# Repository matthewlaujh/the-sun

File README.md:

# the sun — simulator

3D light simulator for a Ø1773 mm LED sun: 2,417 SK6812 RGBW pixels on 25 PCBs, inside the BIG LIGHT 9.1 assembly
(40×80 aluminium ring, wall mount, stand, 3 mm opal diffuser and an 8 mm cast-acrylic dome with a sanded outer face).

**Open `index.html`** — or the hosted copy on GitHub Pages once enabled. Everything is in the one file (Three.js is loaded from jsdelivr).

## What it does
- Renders every pixel at its KiCad position and lights it from the exact bytes that would go on the wire
  (pattern → master → cap 0.90 → gamma 2.2 → 8-bit RGBW), so what you see is what the PixLite E4-S receives.
- Physical diffuser model: cos⁴ screen law on the opal (≈56 mm equivalent height, ~50 % transmission) and on the
  dome (clear cast PMMA, 91 % LT @ 3 mm, outer face sanded), so blur grows from ~72 mm at the rim to ~280 mm at the centre.
- 52 patterns: *Rim ↔ dome* and *Dome studies* written for those optics, a few show patterns, and the four first-light tests.
- Output tab: power per PSU zone, frame stats, hover any LED for index / run / universe / channel / bytes.
- Live tab: point it at the ESP32-GATEWAY's WebSocket (raw 2417×4 frame or DDP packets) and it mirrors the real sun.
- Build tab: toggle assembly layers, exposure, room light; **Explode** slider pulls the layers apart.

## Control chain
Animation host (Olimex ESP32-GATEWAY, standalone AP + web server) → Ethernet → PixLite E4-S Mk3 in EXPANDED mode
→ 8 data runs → 25 boards. DDP on UDP :4048, byte offset = 4·i. `firmware/sun_map.h` carries the same map for C++.

## Layout
- `index.html` — the simulator (self-contained, 4.4 MB)
- `sun-map.json`, `sun-map.csv` — the authoritative pixel map
- `firmware/sun_map.h` — pixel map as C arrays (int16 mm×10) with universe/channel/zone helpers
- `source/` — `template.html` (the page before data is inlined), `sun_data.js` + `sun_model.js` (generated),
  `build_data.py` (map → data + header), `tess.py` / `export_model.py` (STEP → mesh pack), `assemble.py` (builds index.html)

## Rules baked in
Global brightness cap 0.90 · gamma 2.2 at output only · W channel for whites · hang rotation is view-only, pixels are never remapped.

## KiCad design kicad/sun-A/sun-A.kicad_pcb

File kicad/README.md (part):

# the sun — KiCad projects (draft 3)

Generated 2026-09-03 from the 2026-08-17 Studio DXF pack (sun-layout-dxf v2, on-line mounting).
Format: KiCad 8 s-expressions — KiCad 9 opens these and migrates them on save.

## Layout
- `sun-lib/` — shared symbols (`sun.kicad_sym`) + footprints (`sun.pretty/`)
- `sun-A/` — disc, 173 LEDs (172 + centre pixel), Ø448 mm
- `sun-B/` — wedge, 109 LEDs, r226→674, ×12
- `sun-C/` — wedge, 78 LEDs, r676→854, ×12
- per project: `.kicad_pro`, `.kicad_sch`, `.kicad_pcb`, `bom.csv`, `cpl.csv` (JLC format)

## Conventions (match Sun PCB Studio notes)
- Board coordinates: KiCad (x, y) = Studio/DXF (x, −y). No mirror: KiCad front = LED side = DXF view.
- **LED orientation is uniform-radial (draft 3.10)**: every LED's top edge (DIN/VDD side)
  faces AWAY from the sun centre, so the GND pad corner sits bottom-right radially on
  every LED, and every cap sits in the identical spot beside its LED's 5V pin
  (LED-local (−2.45, +4.40), long axis radial). Deviation from the Studio chain-rule pack.
- Data chain: LED pad2 DIN (+x local), pad4 DOUT (−x local); serpentine per Studio ROUTING layer.
- Nets: +5V (F.Cu pour), GND (B.Cu pour), D0 (J_IN→LED1), D1..D(n−1) chain, Dn (LEDn→J_OUT).
- WAGO 2601-3104 poles: **[5V | GND | GND | DATA]**, pads (1,2)(3,4)(5,6)(7,8); lever faces disc centre; **mounted on the BACK side** (same side as the standoffs, opposite the LEDs). Pole order runs mirrored vs a front mount — silk labels on the back read correctly from the wiring side.
- **WAGOs relocated clear of the mounting-plate strips** (30 mm skeleton members on the seam lines), deviation from the Studio pack:
  - **A**: the pair sits exactly diametrically opposite on the E–W line — J_IN at 0 deg (east), J_OUT at 180 deg (west), both at r = 192 mm, clear of the hub-spoke plates.
  - **B/C**: connectors are **docked parallel to their radial (wedge-cut) edge** — pole row along the edge direction, lever facing inboard. Pin-row centres 21.5 mm from the edge; courtyards ≥16 mm clear of the edge vs ~14 mm plate coverage.
- MH standoff footprints are true back-side footprints (placement side = Bottom).
- Standoffs: NPTH Ø4.22 + Ø6.2 pad on B.Cu (bottom reflow), net GND.
- A's DIN feed + C's DOUT return run on B.Cu through the GND pour (via at the LED end).

## Draft 3.15 changes (A connector centring + uniform standoff radius)
- **A's WAGO pair recentred**: pin centre moved from r195 to r199.06 so the
  connector BODY (which extends 10.4mm toward the lever/centre but only 2.3mm
  outward) sits exactly centred between rings 180 and 210; the pin centre was
  already the tangential midpoint of the two nearest LEDs. Still exactly
  opposite on the E-W axis. (Also fixed a sign bug in the placement search
  that tested the courtyard mirrored to the wrong side of the pins.)
- **A's six outer standoffs normalised to a common r=215** (slid inward along
  their radial skeleton members, angles unchanged): the Studio pack had five
  at ~218.5 with the copper moat ON the board edge and one at 215. Now every
  hole has the same ~5.9mm pad-to-edge and 3.5mm moat-to-edge margin.
  WARNING: the matching frame holes move 3.5mm inward on five spokes - update
  the skeleton drawing.

- **No trace under any LED or cap body — either layer** (3.16): LED/cap
  courtyards now keep out foreign traces on the BACK copper too, so the long
  back-layer runs (feeds/returns) weave between footprints instead of passing
  under them. Verified: zero back-copper crossings of any LED/cap body.
- **Pad exits run straight before turning** (3.16): exit stubs lengthened to
  2.5mm from pad centre (~1.75mm beyond the pad edge) and protected from the
  corner-smoothing pass; wrap/jog hooks land with a 1.5mm straight run into
  the DIN pad. Applies across all designs.
- **Fallback links smoothed into curves**: row-to-row jumps and dogleg hops
  (the paths the generic router produces near connectors and standoffs) now go
  through a clearance-validated corner-rounding pass, so they flow like the
  patterned links instead of showing chamfered elbows.

## Draft 3.14 changes (silk-free LED face)
- **All front silkscreen removed** except one mark per LED: the standard
  pin-1/GND TRIANGLE (0.7 mm, filled) tucked UNDER the package body with its
  tip pointing at pad 1 — visible on the bare board for orientation checks,
  completely hidden once the LED is soldered.
- Cap outlines, MH rings, and the front board title are gone; the JLC
  order-number placeholder ("JLCJLCJLCJLC") moved to the BACK silk so JLC's
  print can't land on the front. Board id stays on the back. WAGO pole labels
  (5V/G/G/D), lever mark and pin-1 dot stay on the back silk for hand-wiring.

## Draft 3.13 changes (A chain matches design pack 3)
- Board A's data chain re-ordered to match **sunleddesignpack 3**: the centre LED
  is now the FIRST pixel (universe 1, channel 1) and the serpentine runs in the
  pack-3 (mirrored) direction. LED refs 1..173 = pack3's LED1..173 exactly, so
  the pack's dmx-patch.csv / led-map.csv apply with no hand edits.
  Feed: J_IN -> centre on the back layer; return: LED173 (ring 210) -> J_OUT.
- Only output 1's boards shift in the pack's patch; outputs 2-4 are untouched.
- Mounting stays the BZXC / Ø4.22 layout (user choice; the pack's SMTSO scheme
  was NOT adopted) — centre standoff remains deleted (the centre LED sits there).

## Draft 3.12 changes (isolated mounting holes + A centre pixel)
- **Every mounting hole is now electrically ISOLATED**: the standoff's B.Cu solder
  pad has no net, and a copper-free moat (Ø11 mm keep-out ring, both layers) keeps
  the pours away — a screw scratching through the mask can't short 5V/GND.
  Traces additionally keep ≥3.0 mm from every hole edge (verified ≥2.8).
  Schematic MH pins carry no-connect markers. Standoffs float (not grounded).
- **Board A: centre mounting hole removed, LED173 added at the exact centre** as
  the LAST pixel of the chain (user choice: existing pixel addresses unchanged;
  the new pixel simply appends as A's pixel #173, channels 689-692 in A's map).
  LED172→LED173 runs as a 2-via back-side radial drop; the return LED173→J_OUT
  is a straight back-side shot due west. A now has 173 LEDs, 173 caps, 6 standoffs.

## Draft 3.11 changes (clearances + standoff keep-away)
- **Routing clearances raised** (user: safety margin): trace-to-copper routing target
  0.45 mm (DRC net class stays 0.35 — everything routes with ≥0.1 mm DRC margin),
  courtyard keep-out margin 0.5 mm, and **standoff holes keep all copper ≥2.4 mm
  from the hole edge** (verified ≥2.2 mm; JLC minimum is 0.3).
- No trace passes near a mounting hole any more: a wrap whose band would come
  near a standoff flips to the inward lane, and where the in/out alternation
  can't absorb that, the link takes a short, deterministic **2-via back-side
  jog** instead (A: 3 jogs, B: 1 jog at the row-98→99 jump, C: none).
- Ground stitching: not added — the B.Cu GND plane is the only ground plane
  (F.Cu carries the 5V pour), and the TWO GND vias at every LED (~350/220/160
  per board) already tie front copper to it at ~30 mm pitch everywhere.

## Draft 3.10 changes (uniform LED orientation)
- All LEDs re-oriented to the uniform-radial convention above (same footprint spots,
  the 90/180-degree branch of each rotation re-picked). CPL rotations updated.
- With uniform orientation, in the rings where the chain runs against the LED's
  DOUT→DIN direction the link cannot go straight. Those links use **front-side
  wraps, no vias**: alternating between an inward lane below the row (r_row − 3.75)
  and an outward band above the cap row (r_row + 6.6), as smooth polar arcs.
  Adjacent wraps alternate in/out so nothing crosses.
- The outward band **bulges smoothly around the NPTH standoffs** (4.15 mm keep-out
  envelope with a 2.5 mm ramp) where a mounting hole sits in its path.
- GND vias moved to uniform spots: LED GND via at LED-local (2.45, −2.55) tucked
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
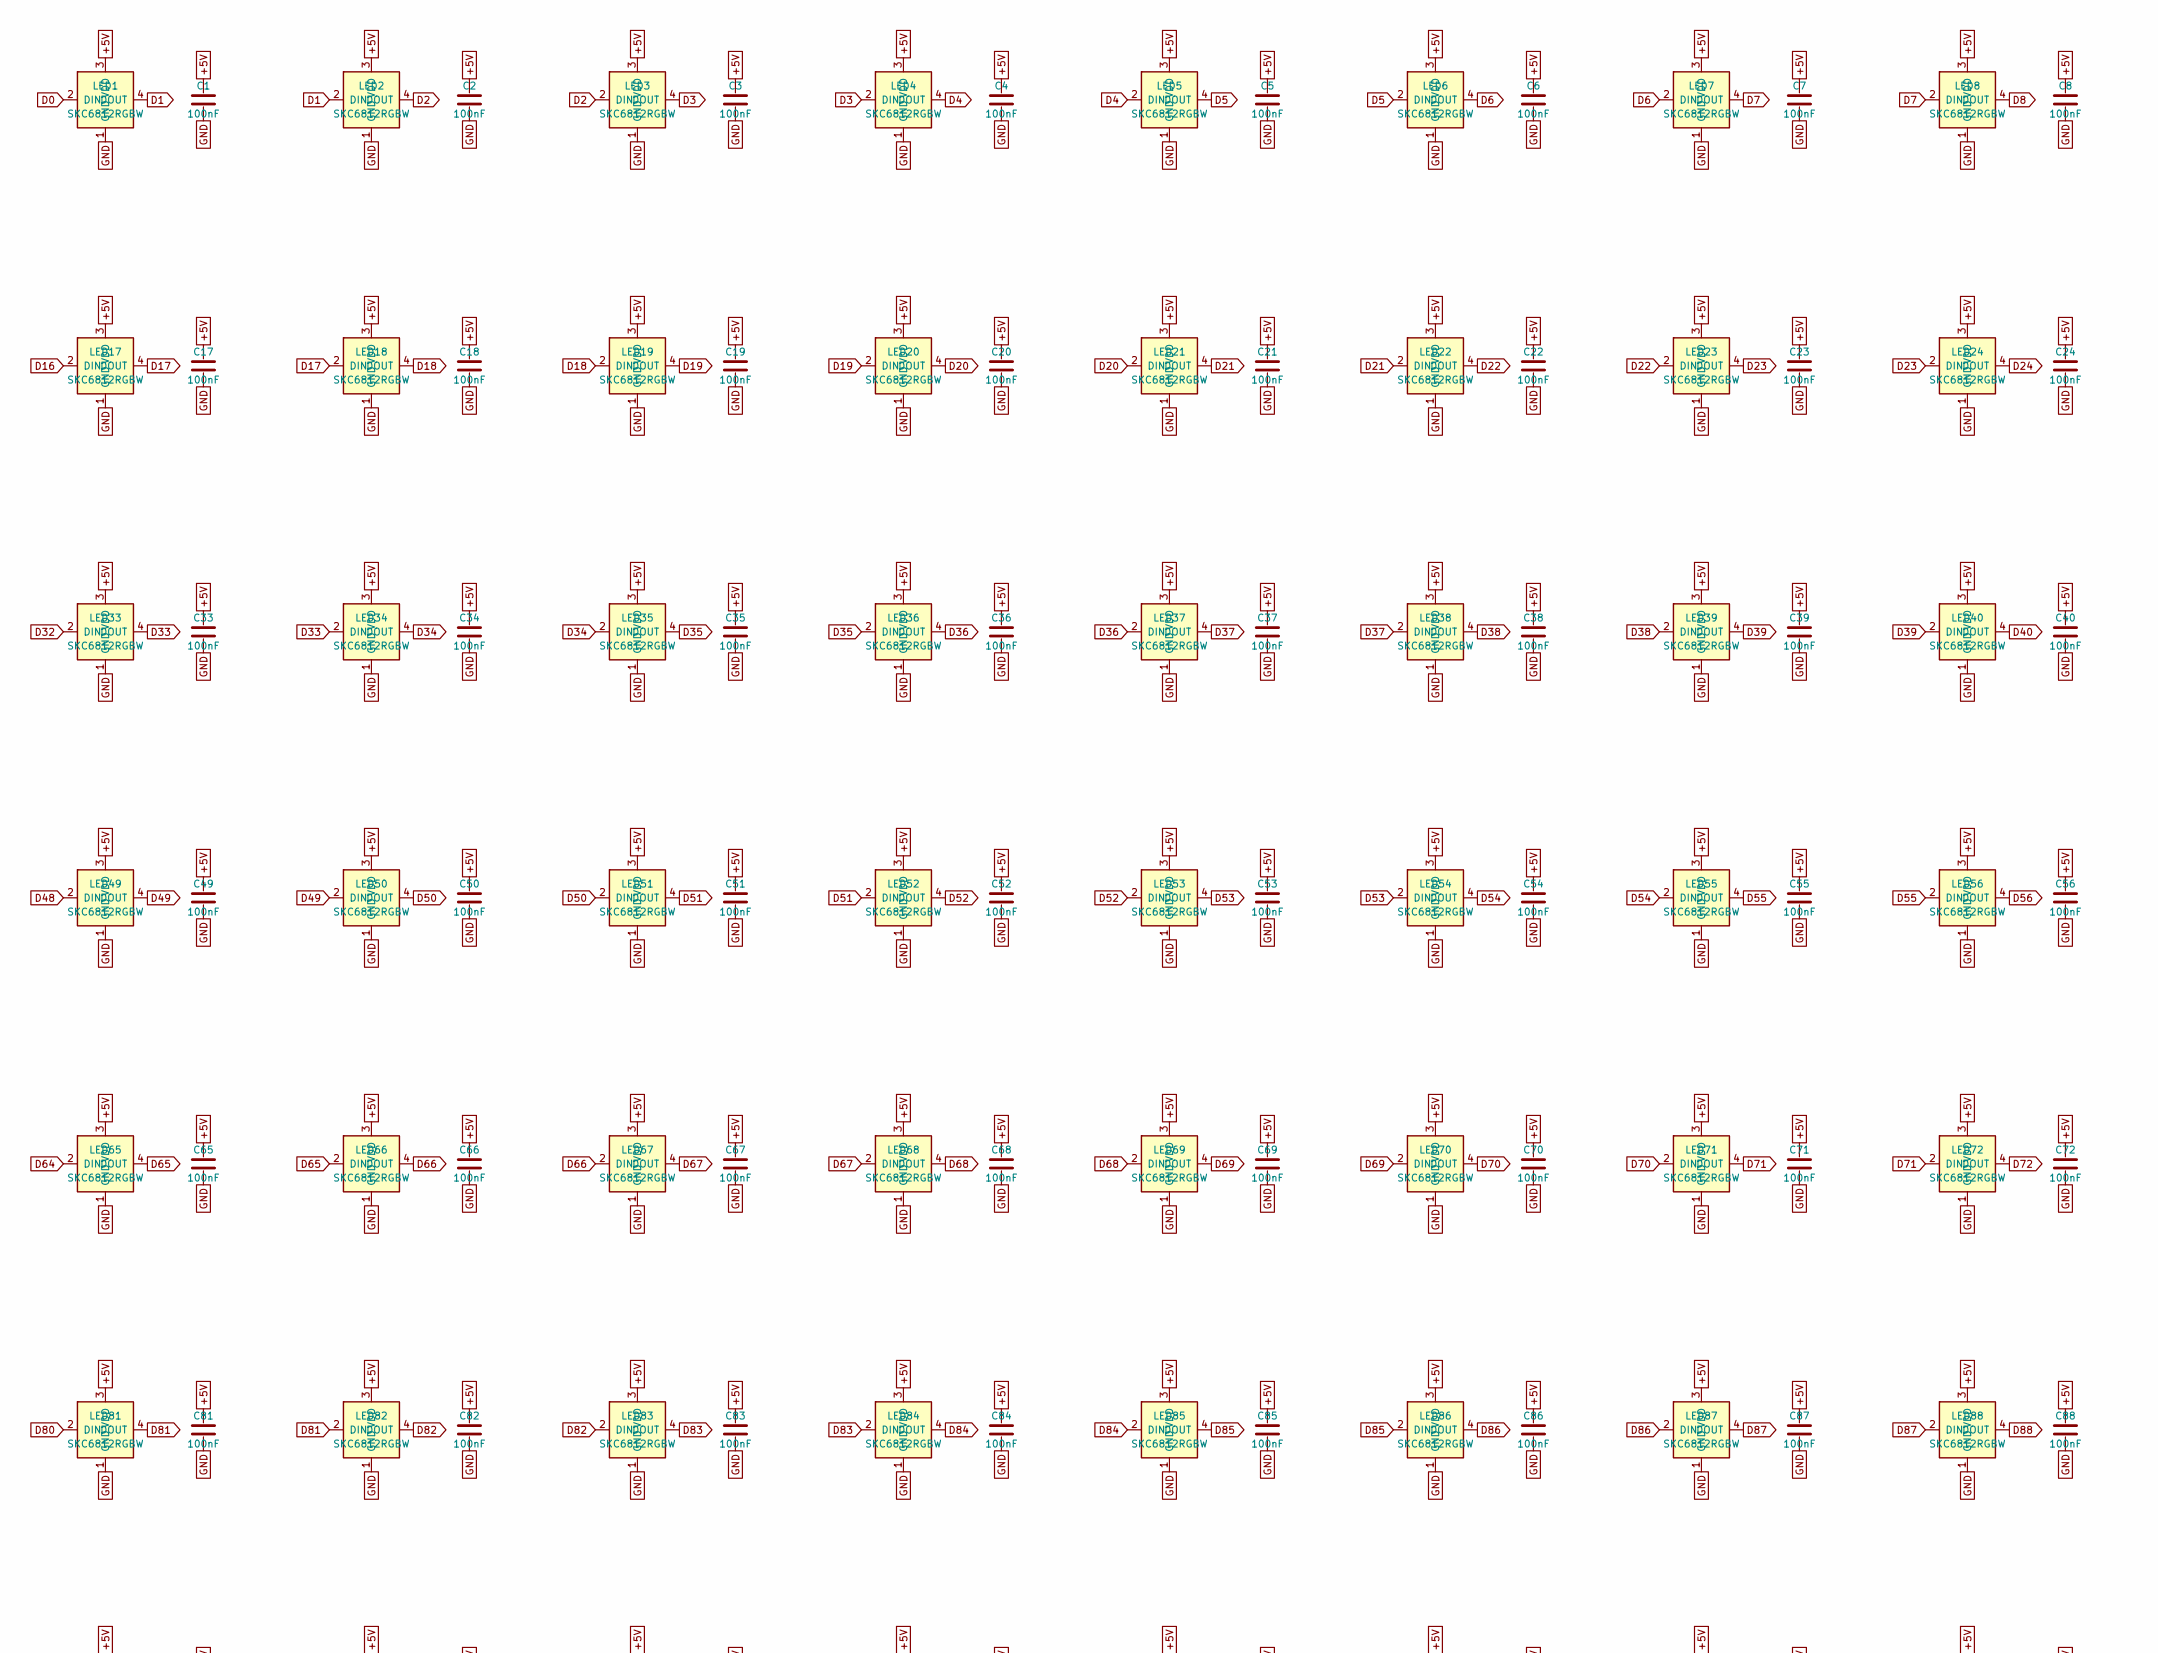
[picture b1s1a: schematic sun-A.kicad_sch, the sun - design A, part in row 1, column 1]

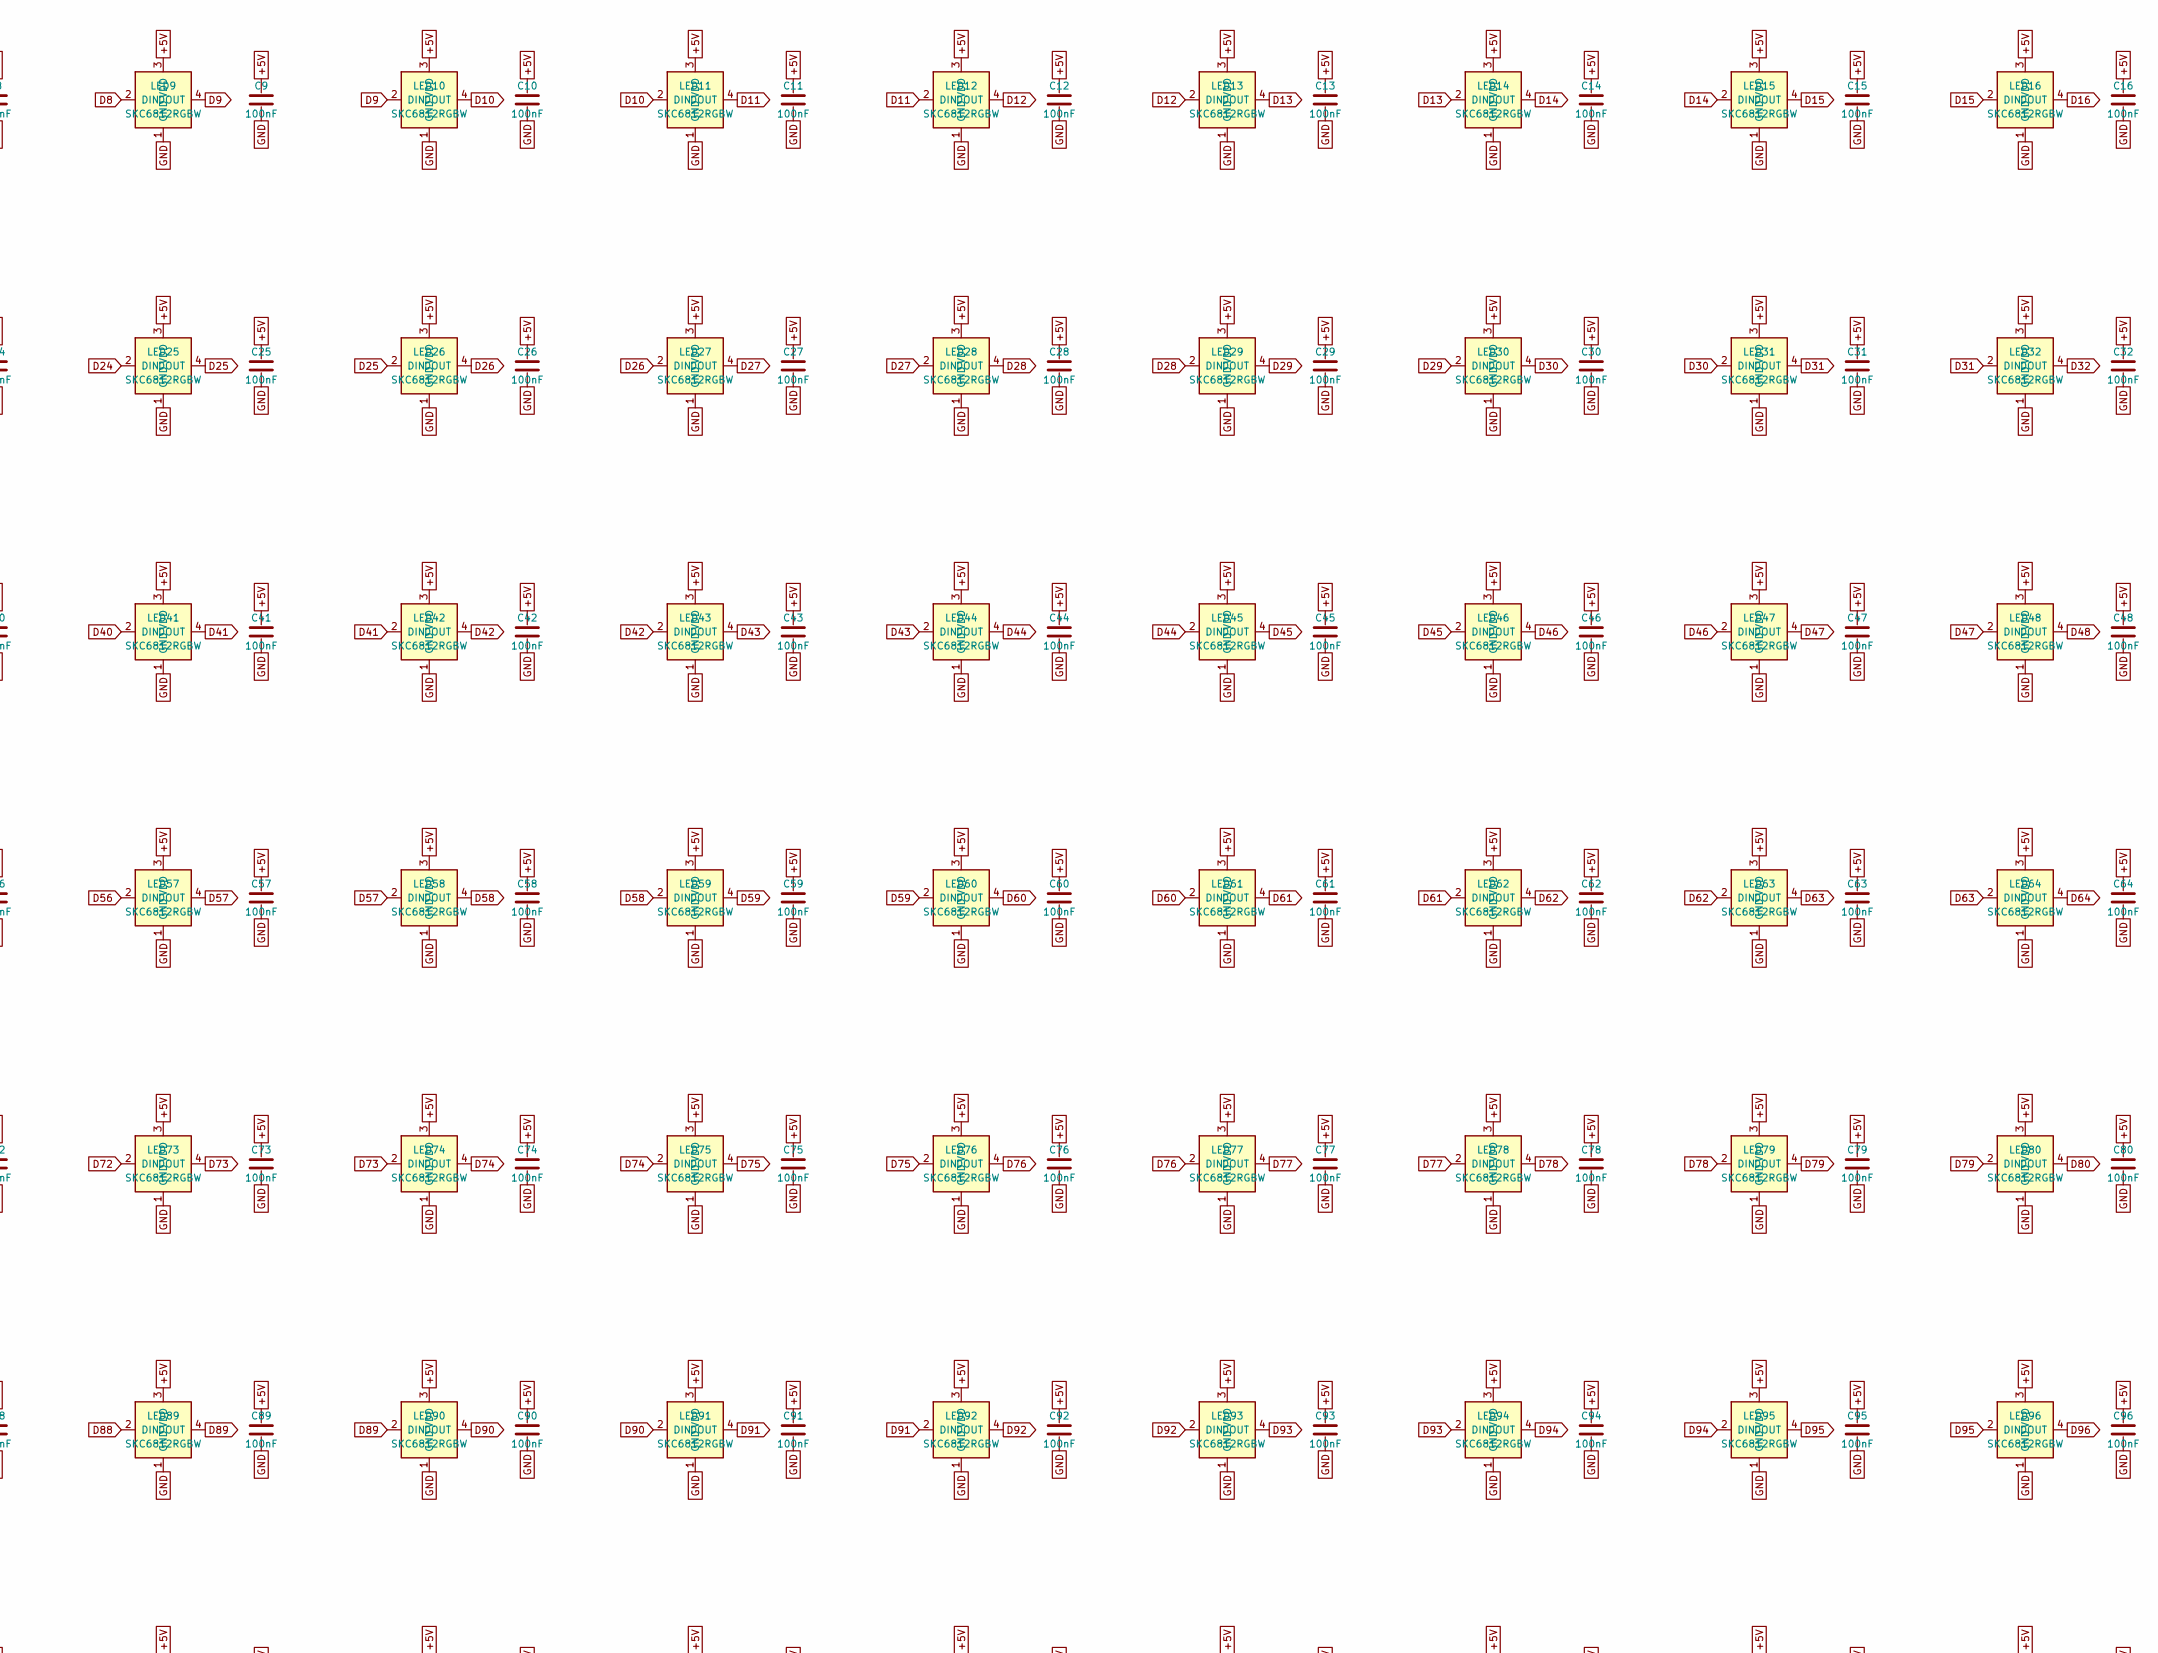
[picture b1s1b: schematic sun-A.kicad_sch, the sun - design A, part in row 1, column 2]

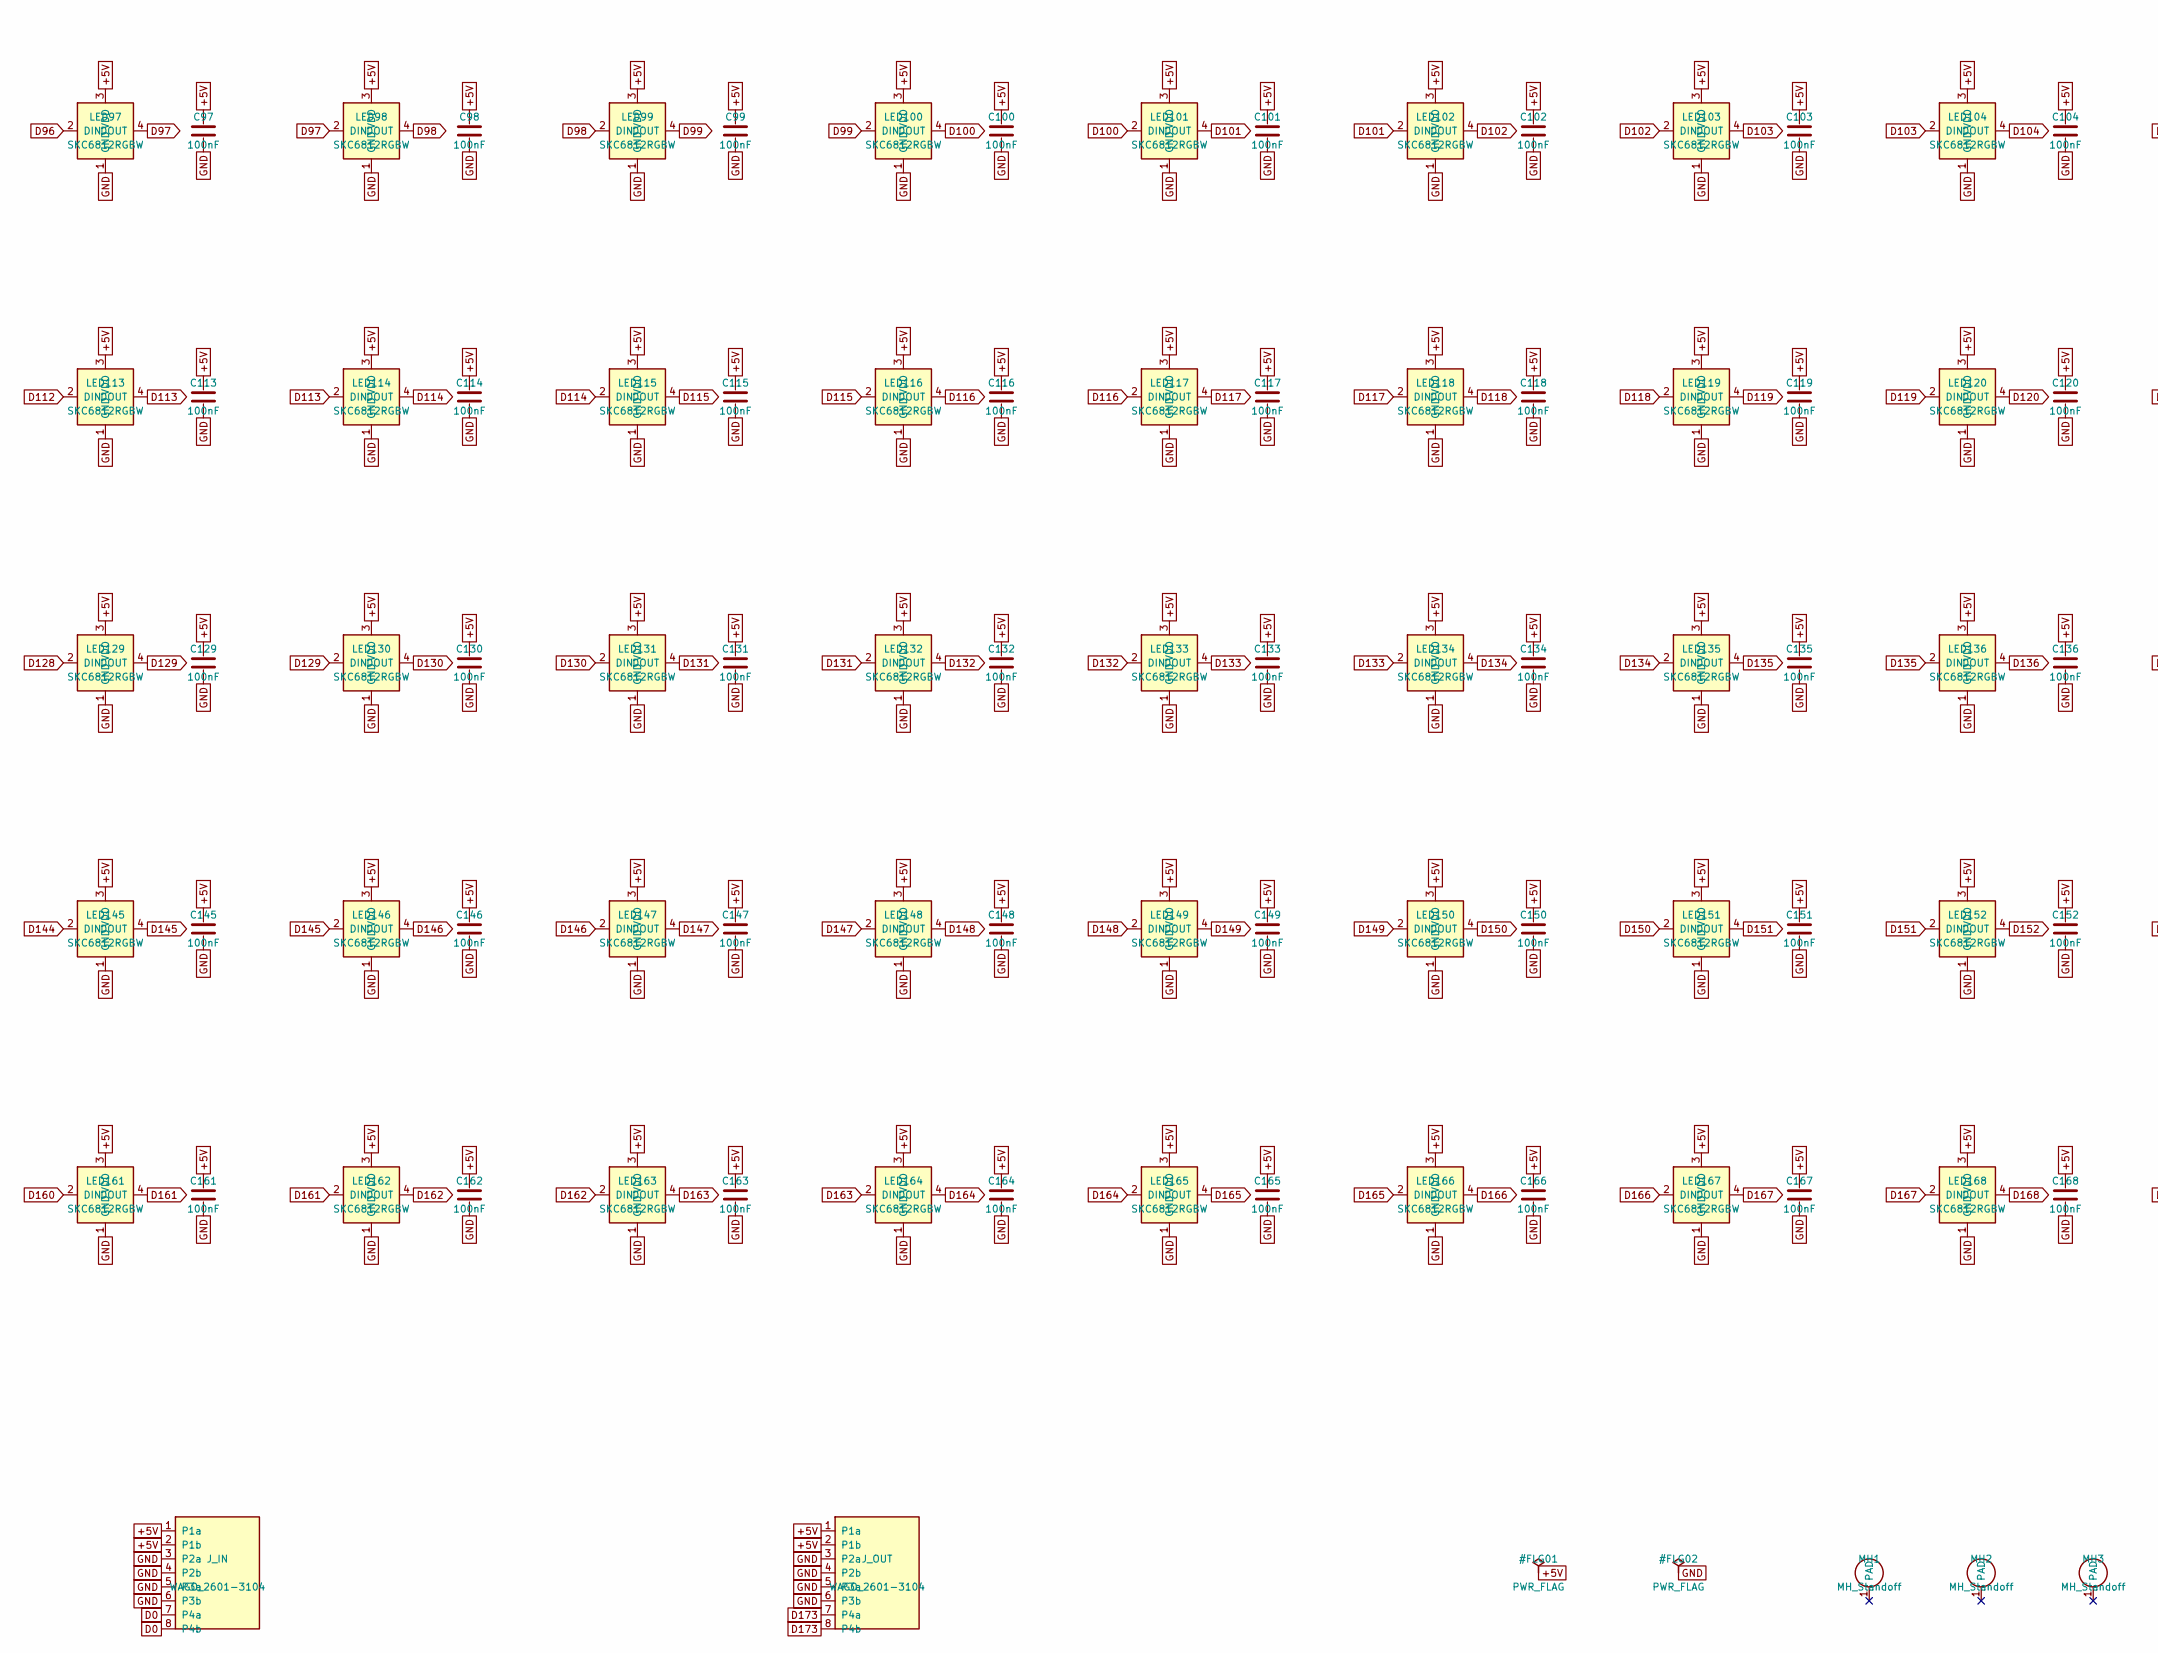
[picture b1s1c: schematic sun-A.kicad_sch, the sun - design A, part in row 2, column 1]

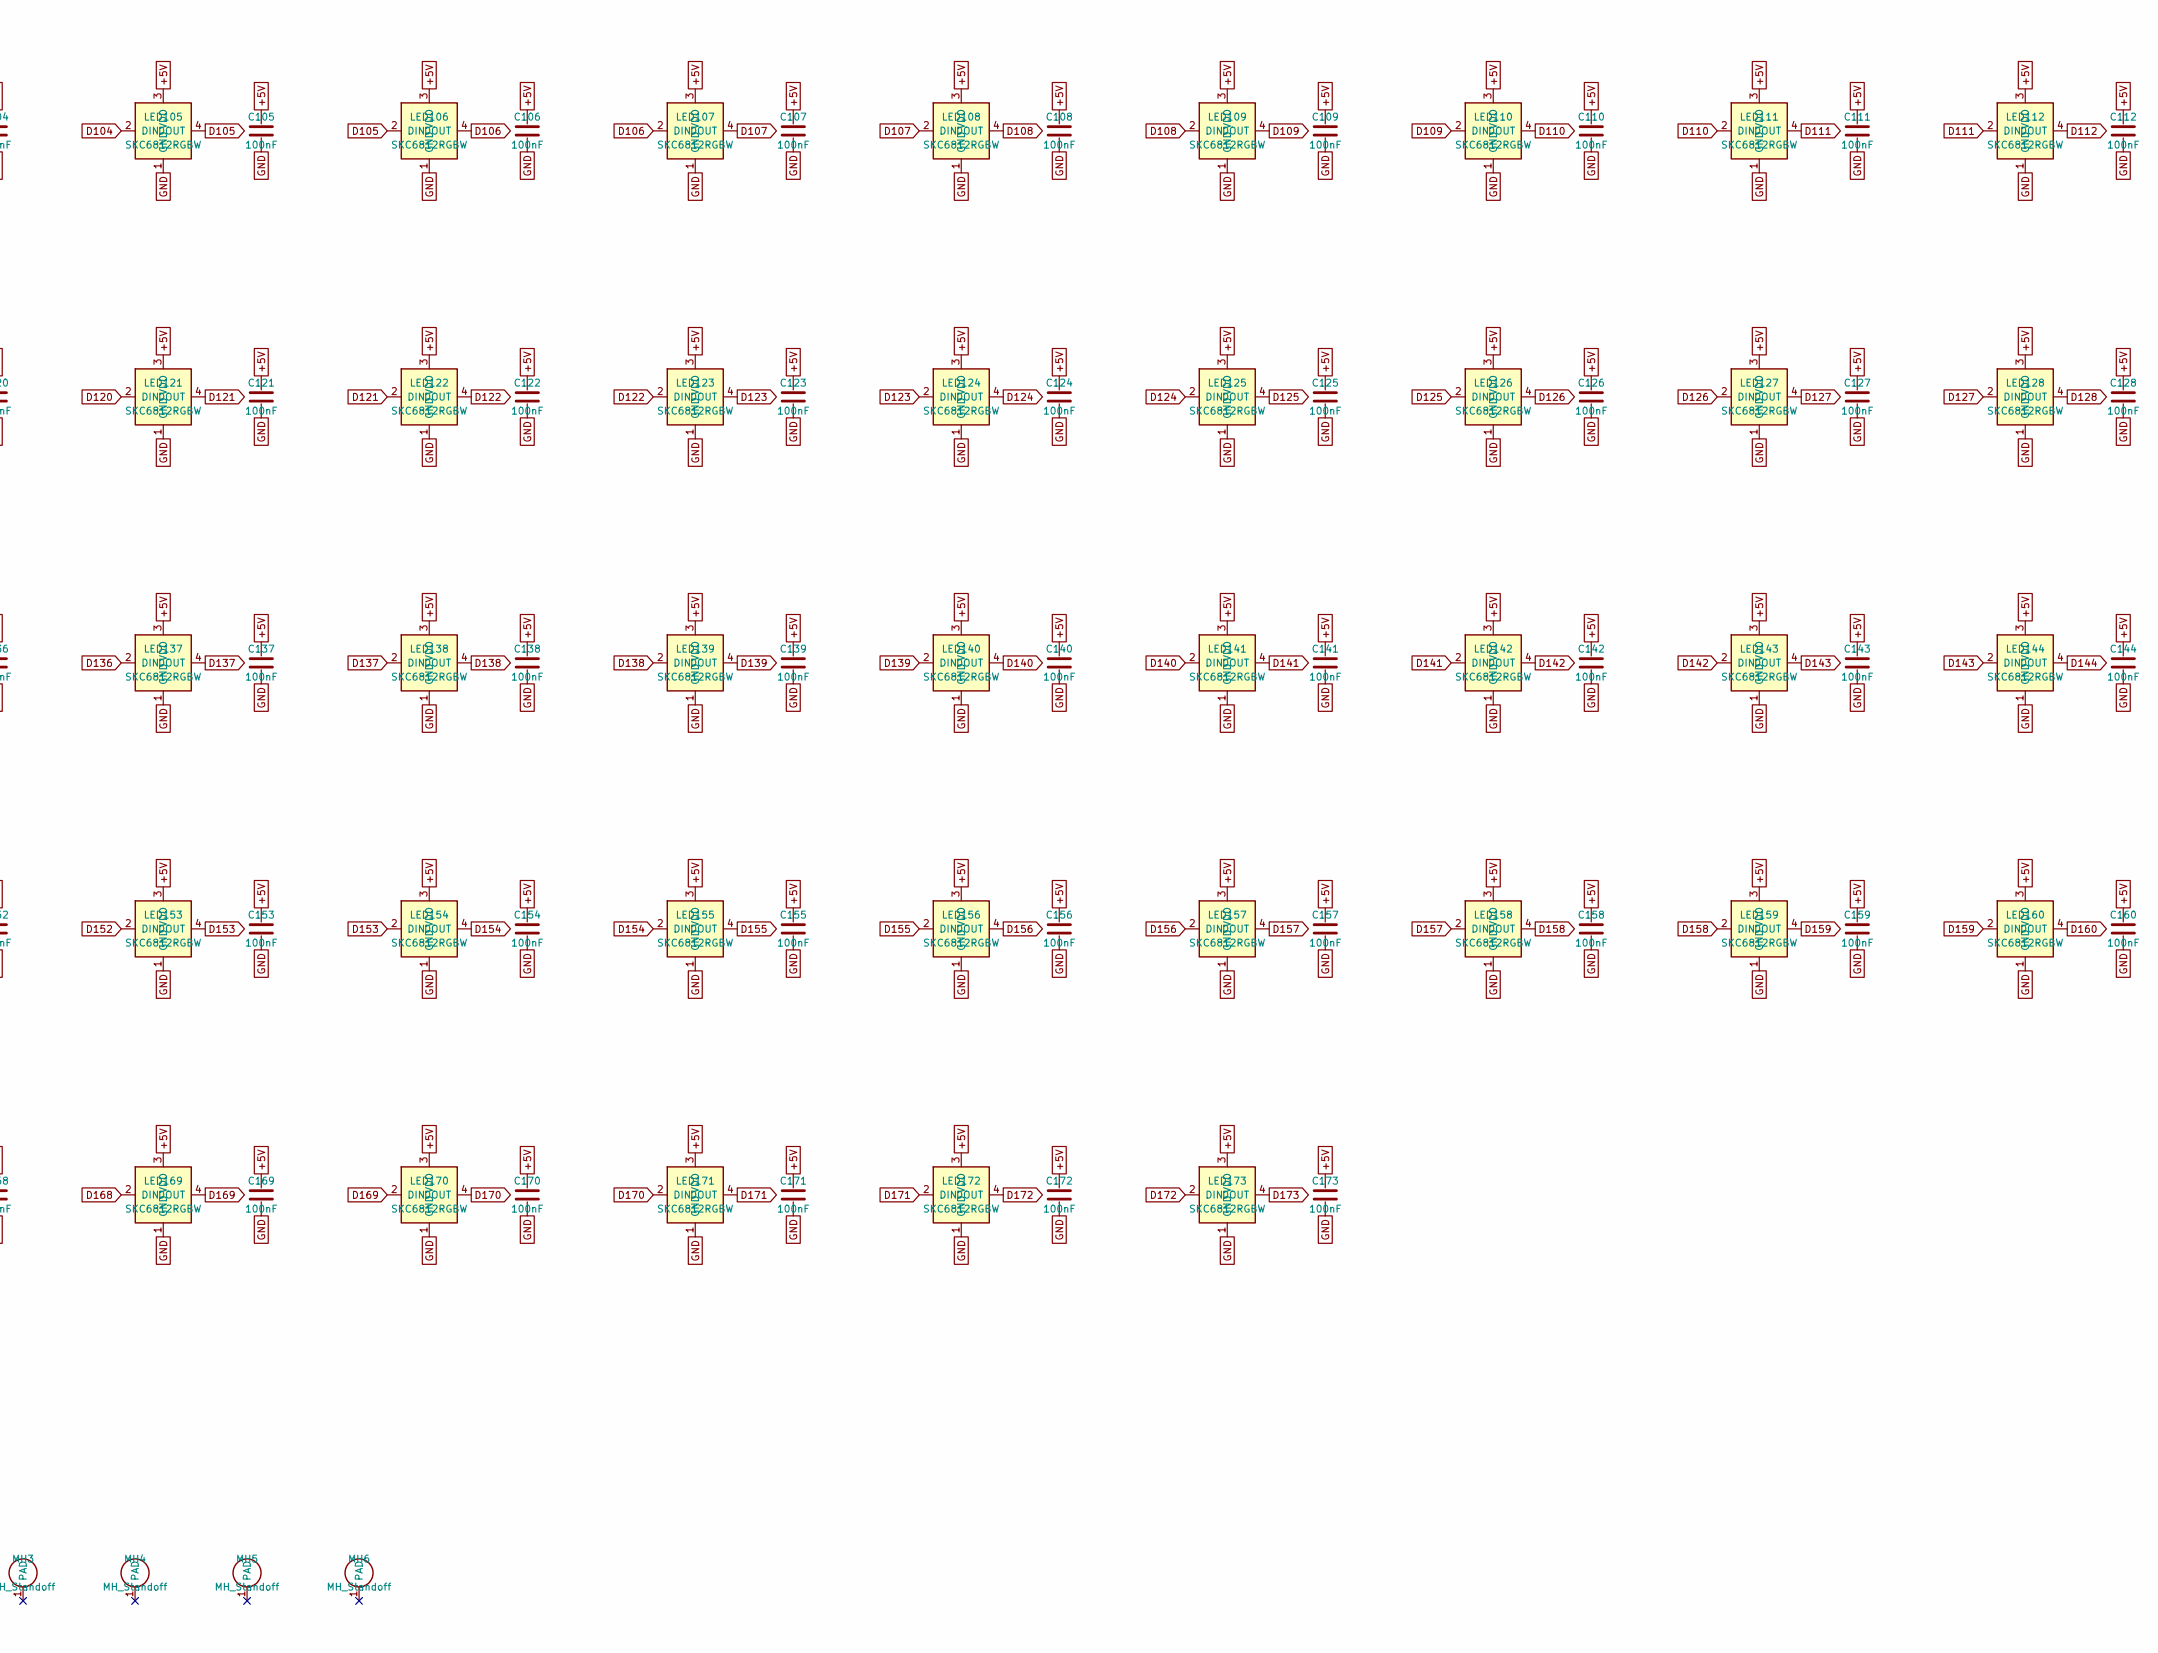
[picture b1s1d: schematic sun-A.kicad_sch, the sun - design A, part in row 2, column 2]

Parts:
C1, C2, C3, C4, C5, C6, C7, C8, C9, C10, C11, C12, C13, C14, C15, C16, C17, C18, C19, C20, C21, C22, C23, C24, C25, C26, C27, C28, C29, C30, C31, C32, C33, C34, C35, C36, C37, C38, C39, C40, C41, C42, C43, C44, C45, C46, C47, C48, C49, C50, C51, C52, C53, C54, C55, C56, C57, C58, C59, C60, C61, C62, C63, C64, C65, C66, C67, C68, C69, C70, C71, C72, C73, C74, C75, C76, C77, C78, C79, C80, C81, C82, C83, C84, C85, C86, C87, C88, C89, C90, C91, C92, C93, C94, C95, C96, C97, C98, C99, C100, C101, C102, C103, C104, C105, C106, C107, C108, C109, C110, C111, C112, C113, C114, C115, C116, C117, C118, C119, C120, C121, C122, C123, C124, C125, C126, C127, C128, C129, C130, C131, C132, C133, C134, C135, C136, C137, C138, C139, C140, C141, C142, C143, C144, C145, C146, C147, C148, C149, C150, C151, C152, C153, C154, C155, C156, C157, C158, C159, C160, C161, C162, C163, C164, C165, C166, C167, C168, C169, C170, C171, C172, C173: 100nF; C_0603_1608Metric; LCSC C1591
J_IN: WAGO_2601-3104; WAGO_2601-3104_THT
J_OUT: WAGO_2601-3104; WAGO_2601-3104_THT
LED1, LED2, LED3, LED4, LED5, LED6, LED7, LED8, LED9, LED10, LED11, LED12, LED13, LED14, LED15, LED16, LED17, LED18, LED19, LED20, LED21, LED22, LED23, LED24, LED25, LED26, LED27, LED28, LED29, LED30, LED31, LED32, LED33, LED34, LED35, LED36, LED37, LED38, LED39, LED40, LED41, LED42, LED43, LED44, LED45, LED46, LED47, LED48, LED49, LED50, LED51, LED52, LED53, LED54, LED55, LED56, LED57, LED58, LED59, LED60, LED61, LED62, LED63, LED64, LED65, LED66, LED67, LED68, LED69, LED70, LED71, LED72, LED73, LED74, LED75, LED76, LED77, LED78, LED79, LED80, LED81, LED82, LED83, LED84, LED85, LED86, LED87, LED88, LED89, LED90, LED91, LED92, LED93, LED94, LED95, LED96, LED97, LED98, LED99, LED100, LED101, LED102, LED103, LED104, LED105, LED106, LED107, LED108, LED109, LED110, LED111, LED112, LED113, LED114, LED115, LED116, LED117, LED118, LED119, LED120, LED121, LED122, LED123, LED124, LED125, LED126, LED127, LED128, LED129, LED130, LED131, LED132, LED133, LED134, LED135, LED136, LED137, LED138, LED139, LED140, LED141, LED142, LED143, LED144, LED145, LED146, LED147, LED148, LED149, LED150, LED151, LED152, LED153, LED154, LED155, LED156, LED157, LED158, LED159, LED160, LED161, LED162, LED163, LED164, LED165, LED166, LED167, LED168, LED169, LED170, LED171, LED172, LED173: SKC6812RGBW; LED_SKC6812RGBW_5050; LCSC C5348912
MH1, MH2, MH3, MH4, MH5, MH6: MH_Standoff; MH_M3_SMT_Standoff_BZXC; LCSC C20617225 (3mm; 30mm variant TBC)

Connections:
+5V: C1.1, C2.1, C3.1, C4.1, C5.1, C6.1, C7.1, C8.1, C9.1, C10.1, C11.1, C12.1, C13.1, C14.1, C15.1, C16.1, C17.1, C18.1, C19.1, C20.1, C21.1, C22.1, C23.1, C24.1, C25.1, C26.1, C27.1, C28.1, C29.1, C30.1, C31.1, C32.1, C33.1, C34.1, C35.1, C36.1, C37.1, C38.1, C39.1, C40.1, C41.1, C42.1, C43.1, C44.1, C45.1, C46.1, C47.1, C48.1, C49.1, C50.1, C51.1, C52.1, C53.1, C54.1, C55.1, C56.1, C57.1, C58.1, C59.1, C60.1, C61.1, C62.1, C63.1, C64.1, C65.1, C66.1, C67.1, C68.1, C69.1, C70.1, C71.1, C72.1, C73.1, C74.1, C75.1, C76.1, C77.1, C78.1, C79.1, C80.1, C81.1, C82.1, C83.1, C84.1, C85.1, C86.1, C87.1, C88.1, C89.1, C90.1, C91.1, C92.1, C93.1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
D0: J_IN.7 (P4a), J_IN.8 (P4b), LED1.2 (DIN)
D1: LED1.4 (DOUT), LED2.2 (DIN)
D2: LED2.4 (DOUT), LED3.2 (DIN)
D3: LED3.4 (DOUT), LED4.2 (DIN)
D4: LED4.4 (DOUT), LED5.2 (DIN)
D5: LED5.4 (DOUT), LED6.2 (DIN)
D6: LED6.4 (DOUT), LED7.2 (DIN)
D7: LED7.4 (DOUT), LED8.2 (DIN)
D8: LED8.4 (DOUT), LED9.2 (DIN)
D9: LED9.4 (DOUT), LED10.2 (DIN)
D10: LED10.4 (DOUT), LED11.2 (DIN)
D11: LED11.4 (DOUT), LED12.2 (DIN)
D12: LED12.4 (DOUT), LED13.2 (DIN)
D13: LED13.4 (DOUT), LED14.2 (DIN)
D14: LED14.4 (DOUT), LED15.2 (DIN)
D15: LED15.4 (DOUT), LED16.2 (DIN)
D16: LED16.4 (DOUT), LED17.2 (DIN)
D17: LED17.4 (DOUT), LED18.2 (DIN)
D18: LED18.4 (DOUT), LED19.2 (DIN)
D19: LED19.4 (DOUT), LED20.2 (DIN)
D20: LED20.4 (DOUT), LED21.2 (DIN)
D21: LED21.4 (DOUT), LED22.2 (DIN)
D22: LED22.4 (DOUT), LED23.2 (DIN)
D23: LED23.4 (DOUT), LED24.2 (DIN)
D24: LED24.4 (DOUT), LED25.2 (DIN)
D25: LED25.4 (DOUT), LED26.2 (DIN)
D26: LED26.4 (DOUT), LED27.2 (DIN)
D27: LED27.4 (DOUT), LED28.2 (DIN)
D28: LED28.4 (DOUT), LED29.2 (DIN)
D29: LED29.4 (DOUT), LED30.2 (DIN)
D30: LED30.4 (DOUT), LED31.2 (DIN)
D31: LED31.4 (DOUT), LED32.2 (DIN)
D32: LED32.4 (DOUT), LED33.2 (DIN)
D33: LED33.4 (DOUT), LED34.2 (DIN)
D34: LED34.4 (DOUT), LED35.2 (DIN)
D35: LED35.4 (DOUT), LED36.2 (DIN)
D36: LED36.4 (DOUT), LED37.2 (DIN)
D37: LED37.4 (DOUT), LED38.2 (DIN)
D38: LED38.4 (DOUT), LED39.2 (DIN)
D39: LED39.4 (DOUT), LED40.2 (DIN)
D40: LED40.4 (DOUT), LED41.2 (DIN)
D41: LED41.4 (DOUT), LED42.2 (DIN)
D42: LED42.4 (DOUT), LED43.2 (DIN)
D43: LED43.4 (DOUT), LED44.2 (DIN)
D44: LED44.4 (DOUT), LED45.2 (DIN)
D45: LED45.4 (DOUT), LED46.2 (DIN)
D46: LED46.4 (DOUT), LED47.2 (DIN)
D47: LED47.4 (DOUT), LED48.2 (DIN)
D48: LED48.4 (DOUT), LED49.2 (DIN)
D49: LED49.4 (DOUT), LED50.2 (DIN)
D50: LED50.4 (DOUT), LED51.2 (DIN)
D51: LED51.4 (DOUT), LED52.2 (DIN)
D52: LED52.4 (DOUT), LED53.2 (DIN)
D53: LED53.4 (DOUT), LED54.2 (DIN)
D54: LED54.4 (DOUT), LED55.2 (DIN)
D55: LED55.4 (DOUT), LED56.2 (DIN)
D56: LED56.4 (DOUT), LED57.2 (DIN)
D57: LED57.4 (DOUT), LED58.2 (DIN)
D58: LED58.4 (DOUT), LED59.2 (DIN)
D59: LED59.4 (DOUT), LED60.2 (DIN)
D60: LED60.4 (DOUT), LED61.2 (DIN)
D61: LED61.4 (DOUT), LED62.2 (DIN)
D62: LED62.4 (DOUT), LED63.2 (DIN)
D63: LED63.4 (DOUT), LED64.2 (DIN)
D64: LED64.4 (DOUT), LED65.2 (DIN)
D65: LED65.4 (DOUT), LED66.2 (DIN)
D66: LED66.4 (DOUT), LED67.2 (DIN)
D67: LED67.4 (DOUT), LED68.2 (DIN)
D68: LED68.4 (DOUT), LED69.2 (DIN)
D69: LED69.4 (DOUT), LED70.2 (DIN)
D70: LED70.4 (DOUT), LED71.2 (DIN)
D71: LED71.4 (DOUT), LED72.2 (DIN)
D72: LED72.4 (DOUT), LED73.2 (DIN)
D73: LED73.4 (DOUT), LED74.2 (DIN)
D74: LED74.4 (DOUT), LED75.2 (DIN)
D75: LED75.4 (DOUT), LED76.2 (DIN)
D76: LED76.4 (DOUT), LED77.2 (DIN)
D77: LED77.4 (DOUT), LED78.2 (DIN)
D78: LED78.4 (DOUT), LED79.2 (DIN)
D79: LED79.4 (DOUT), LED80.2 (DIN)
D80: LED80.4 (DOUT), LED81.2 (DIN)
D81: LED81.4 (DOUT), LED82.2 (DIN)
D82: LED82.4 (DOUT), LED83.2 (DIN)
D83: LED83.4 (DOUT), LED84.2 (DIN)
D84: LED84.4 (DOUT), LED85.2 (DIN)
D85: LED85.4 (DOUT), LED86.2 (DIN)
D86: LED86.4 (DOUT), LED87.2 (DIN)
D87: LED87.4 (DOUT), LED88.2 (DIN)
D88: LED88.4 (DOUT), LED89.2 (DIN)
D89: LED89.4 (DOUT), LED90.2 (DIN)
D90: LED90.4 (DOUT), LED91.2 (DIN)
D91: LED91.4 (DOUT), LED92.2 (DIN)
D92: LED92.4 (DOUT), LED93.2 (DIN)
D93: LED93.4 (DOUT), LED94.2 (DIN)
D94: LED94.4 (DOUT), LED95.2 (DIN)
D95: LED95.4 (DOUT), LED96.2 (DIN)
D96: LED96.4 (DOUT), LED97.2 (DIN)
D97: LED97.4 (DOUT), LED98.2 (DIN)
D98: LED98.4 (DOUT), LED99.2 (DIN)
D99: LED99.4 (DOUT), LED100.2 (DIN)
D100: LED100.4 (DOUT), LED101.2 (DIN)
D101: LED101.4 (DOUT), LED102.2 (DIN)
D102: LED102.4 (DOUT), LED103.2 (DIN)
D103: LED103.4 (DOUT), LED104.2 (DIN)
D104: LED104.4 (DOUT), LED105.2 (DIN)
D105: LED105.4 (DOUT), LED106.2 (DIN)
D106: LED106.4 (DOUT), LED107.2 (DIN)
D107: LED107.4 (DOUT), LED108.2 (DIN)
D108: LED108.4 (DOUT), LED109.2 (DIN)
D109: LED109.4 (DOUT), LED110.2 (DIN)
D110: LED110.4 (DOUT), LED111.2 (DIN)
D111: LED111.4 (DOUT), LED112.2 (DIN)
D112: LED112.4 (DOUT), LED113.2 (DIN)
D113: LED113.4 (DOUT), LED114.2 (DIN)
D114: LED114.4 (DOUT), LED115.2 (DIN)
D115: LED115.4 (DOUT), LED116.2 (DIN)
D116: LED116.4 (DOUT), LED117.2 (DIN)
D117: LED117.4 (DOUT), LED118.2 (DIN)
D118: LED118.4 (DOUT), LED119.2 (DIN)
D119: LED119.4 (DOUT), LED120.2 (DIN)
D120: LED120.4 (DOUT), LED121.2 (DIN)
D121: LED121.4 (DOUT), LED122.2 (DIN)
D122: LED122.4 (DOUT), LED123.2 (DIN)
D123: LED123.4 (DOUT), LED124.2 (DIN)
D124: LED124.4 (DOUT), LED125.2 (DIN)
D125: LED125.4 (DOUT), LED126.2 (DIN)
D126: LED126.4 (DOUT), LED127.2 (DIN)
D127: LED127.4 (DOUT), LED128.2 (DIN)
D128: LED128.4 (DOUT), LED129.2 (DIN)
D129: LED129.4 (DOUT), LED130.2 (DIN)
D130: LED130.4 (DOUT), LED131.2 (DIN)
D131: LED131.4 (DOUT), LED132.2 (DIN)
D132: LED132.4 (DOUT), LED133.2 (DIN)
D133: LED133.4 (DOUT), LED134.2 (DIN)
D134: LED134.4 (DOUT), LED135.2 (DIN)
D135: LED135.4 (DOUT), LED136.2 (DIN)
D136: LED136.4 (DOUT), LED137.2 (DIN)
D137: LED137.4 (DOUT), LED138.2 (DIN)
D138: LED138.4 (DOUT), LED139.2 (DIN)
D139: LED139.4 (DOUT), LED140.2 (DIN)
D140: LED140.4 (DOUT), LED141.2 (DIN)
D141: LED141.4 (DOUT), LED142.2 (DIN)
D142: LED142.4 (DOUT), LED143.2 (DIN)
D143: LED143.4 (DOUT), LED144.2 (DIN)
D144: LED144.4 (DOUT), LED145.2 (DIN)
D145: LED145.4 (DOUT), LED146.2 (DIN)
D146: LED146.4 (DOUT), LED147.2 (DIN)
D147: LED147.4 (DOUT), LED148.2 (DIN)
D148: LED148.4 (DOUT), LED149.2 (DIN)
D149: LED149.4 (DOUT), LED150.2 (DIN)
D150: LED150.4 (DOUT), LED151.2 (DIN)
D151: LED151.4 (DOUT), LED152.2 (DIN)
D152: LED152.4 (DOUT), LED153.2 (DIN)
D153: LED153.4 (DOUT), LED154.2 (DIN)
D154: LED154.4 (DOUT), LED155.2 (DIN)
D155: LED155.4 (DOUT), LED156.2 (DIN)
D156: LED156.4 (DOUT), LED157.2 (DIN)
D157: LED157.4 (DOUT), LED158.2 (DIN)
D158: LED158.4 (DOUT), LED159.2 (DIN)
D159: LED159.4 (DOUT), LED160.2 (DIN)
D160: LED160.4 (DOUT), LED161.2 (DIN)
D161: LED161.4 (DOUT), LED162.2 (DIN)
D162: LED162.4 (DOUT), LED163.2 (DIN)
D163: LED163.4 (DOUT), LED164.2 (DIN)
D164: LED164.4 (DOUT), LED165.2 (DIN)
D165: LED165.4 (DOUT), LED166.2 (DIN)
D166: LED166.4 (DOUT), LED167.2 (DIN)
D167: LED167.4 (DOUT), LED168.2 (DIN)
D168: LED168.4 (DOUT), LED169.2 (DIN)
D169: LED169.4 (DOUT), LED170.2 (DIN)
D170: LED170.4 (DOUT), LED171.2 (DIN)
D171: LED171.4 (DOUT), LED172.2 (DIN)
D172: LED172.4 (DOUT), LED173.2 (DIN)
D173: J_OUT.7 (P4a), J_OUT.8 (P4b), LED173.4 (DOUT)
GND: C1.2, C2.2, C3.2, C4.2, C5.2, C6.2, C7.2, C8.2, C9.2, C10.2, C11.2, C12.2, C13.2, C14.2, C15.2, C16.2, C17.2, C18.2, C19.2, C20.2, C21.2, C22.2, C23.2, C24.2, C25.2, C26.2, C27.2, C28.2, C29.2, C30.2, C31.2, C32.2, C33.2, C34.2, C35.2, C36.2, C37.2, C38.2, C39.2, C40.2, C41.2, C42.2, C43.2, C44.2, C45.2, C46.2, C47.2, C48.2, C49.2, C50.2, C51.2, C52.2, C53.2, C54.2, C55.2, C56.2, C57.2, C58.2, C59.2, C60.2, C61.2, C62.2, C63.2, C64.2, C65.2, C66.2, C67.2, C68.2, C69.2, C70.2, C71.2, C72.2, C73.2, C74.2, C75.2, C76.2, C77.2, C78.2, C79.2, C80.2, C81.2, C82.2, C83.2, C84.2, C85.2, C86.2, C87.2, C88.2, C89.2, C90.2, C91.2, C92.2, C93.2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
